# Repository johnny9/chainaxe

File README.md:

# ChainAxe — Rev A.1

Status: **engineering prototype; not a manufacturing release**  
Updated: 2026-08-16

ChainAxe is a clean-room ESP32-S3 controller for:

- one full S19- or S21-family Bitmain hashboard through the common data cable;
- four AntHat-style 12 V, four-wire Antminer fans with tach feedback and fail-safe full-speed startup;
- a 12–15 V low-current controller input; and
- native USB, Wi-Fi, and an ESP-Miner-derived mining application.

ChainAxe is an independent open-hardware project and is not affiliated with or endorsed by Bitmain. Antminer is a trademark of its respective owner.

The name refers to the complete ASIC hash chain controlled by the board. ChainAxe supersedes the earlier FT4232HQ-based **bitcrane** prototype with a clean ESP32-S3 architecture intended to run ESP-Miner directly.

There is **no PSU communication interface in Rev A.1**. Hashboard ASIC/core power remains on its normal external bus bars or bench supply. The ESP board communicates only through the hashboard data cable and drives the four fan connectors.

## Connector interpretation

The retained hashboard connector is physically **2×9 / 18 positions**. Pins 1–16 are used and positions 17–18 are NC, which explains the shorthand “16-pin header.” The user has confirmed this interface is compatible across the intended S19/S21 targets, so Rev A.1 standardizes the cable-side logic domain at 3.3 V and removes the previous target-voltage population matrix.

Compatibility here means the connector and electrical interface are shared. Firmware must still select the correct ASIC family, chip count, address stride, baud sequence, reset policy, and voltage/temperature-control path for the exact hashboard SKU.

## What is here

| Area | Deliverable |
|---|---|
| Architecture | Rail, signal, safety, and power-up decisions in `docs/architecture.md` |
| Target matrix | S19/S21 ASIC/profile scope in `docs/target-matrix.md` |
| Interfaces | Hashboard, fan, power, and USB pin tables in `docs/connector-pinout.md` |
| Schematic entry | Sheet plan and explicit net map in `schematic/` |
| BOM | JLC-oriented engineering BOM and upload template in `bom/` |
| PCB start | 100 × 70 mm floorplan, placement table, stack-up, and routing rules in `pcb/` and `docs/pcb-layout.md` |
| Firmware | ESP-Miner multi-profile porting plan in `firmware/esp-miner-porting-plan.md` |
| Release gates | Review and first-power checklist in `design-review-checklist.md` |
| Validation | Frozen hashes, automated results, and explicit open gates in `VALIDATION.md` |
| Provenance | Repository commits, licenses, and primary datasheets in `sources.md` |

## KiCad project

The editable KiCad 9 baseline is under `hardware/chainaxe/`:

- `chainaxe.kicad_pro` — project and net-class settings;
- `chainaxe.kicad_sch` — preliminary electrical schematic; and
- `chainaxe.kicad_pcb` — 100 × 70 mm unrouted placement baseline.

The KiCad files are intended for engineering review and iteration. They are not released Gerbers. Parts marked provisional or TBD in the engineering BOM must be resolved, the exact connector footprints must be fit-checked, and ERC/DRC must pass in KiCad before an order is placed. KiCad's CLI is not available in this workspace, so the included automated structural, pin-map, and placement-geometry checks are not ERC/DRC results.

The BOM distinguishes exact part candidates from provisional and TBD choices. There are no Gerbers, CPL, or fabrication ZIPs because the exact connector footprints, fan current path, and first supported hashboard profile still require engineering signoff.

## Rev A.1 block architecture

```mermaid
flowchart TD
    F12["12 V fan input"] --> FUSE["External fuse"]
    FUSE --> RPP["Reverse-polarity FETs"]
    RPP --> FANS["Four AntHat-style fan headers"]
    VIN["12–15 V logic input"] --> BUCK["3.3 V logic buck"]
    F12 -. "optional link at 12 V only" .-> BUCK
    USB["USB-C 5 V"] --> BUCK
    BUCK --> ESP["ESP32-S3"]
    ESP --> FANCTL["EMC2305 + fail-safe sinks"]
    ESP --> HBIO["3.3 V gated hashboard interface"]
    HBIO --> HB["18-position / 16-used cable"]
```

The hashboard's ASIC/core current does **not** pass through this controller. Controller ground, fan ground, and hashboard data-cable ground must be common.

## Power-input decision

- `J1 FAN_12V_IN`: high-current, regulated 12 V for the four fans.
- `J6 VIN_LOGIC_12_15`: low-current 12–15 V input for the AP64501 logic regulator.
- `JP1 FAN_TO_LOGIC`: optional fitted link/diode that powers logic from J1 when J1 is verified 12 V.
- USB-C can power logic for flashing with J1/J6 disconnected.

This split is intentional. A nominal 12 V fan must not receive 15 V unless its actual datasheet explicitly permits it. A single 12 V source can power both rails by fitting JP1; a 13–15 V hashboard system needs a separate regulated 12 V fan feed or a future high-current 12 V converter.

## Primary target profiles

- S19 XP / S19k-class BM1366 boards: ASIC driver exists in ESP-Miner; full-board chip counts and power control remain profile-specific.
- S21 BM1368 boards: ASIC driver exists; standard S21 evidence uses 108 chips and requires a NoPIC-aware startup path.
- S21 Pro / S21 XP / S21+ BM1370 boards: chip driver exists; each SKU has a different chip count.
- BM1398 and BM1362 S19-family boards require new ESP-Miner drivers before mining, even though the connector hardware is compatible. The family name alone is not sufficient to select the ASIC.

See `docs/target-matrix.md` for exact scope and evidence levels.

## Recommended first article

1. Review the KiCad schematic pin-by-pin, fit-check every connector and project-local footprint against current manufacturer drawings and real mating parts, and run ERC.
2. Assemble USB, ESP32-S3, AP64501, EMC2305, fan buffer/sinks, and the standardized 3.3 V hashboard interface.
3. Hand-install the 12 V fan, 12–15 V logic, fan, and hashboard connectors on five boards.
4. Validate USB-only and logic-only power first.
5. Validate four genuine Antminer fans from the dedicated 12 V input.
6. Bring up one named hashboard profile with core power current-limited and mining disabled until enumeration, temperatures, and fan interlocks pass.

## Key design choices

- ESP32-S3-WROOM-1-N16R8 retains ESP-Miner's UART pins 17/18.
- A SN74AXC4T774-class buffer operates at 3.3 V on both sides and provides explicit interface enable/disable.
- TPS22917 supplies connector pin 16 with controlled turn-on and reverse-current blocking.
- TMUX1511 is powered from switched `HB_3V3` and uses two of its powered-off-protected channels for the hashboard I²C pair. Local pull-ups stay on controller `3V3`; cable-side pull-ups stay on `HB_3V3`, so an unpowered cable domain cannot be phantom-powered through SDA/SCL.
- RESET has no universal hardware pulldown. Its bias and use are profile-dependent, and the series `RESET_ENABLE_LINK` is DNP/open in the default S21-safe assembly. It is populated with 33 Ω only for a specifically validated legacy-reset profile.
- EMC2305 outputs pass through a disabled-by-default SN74LVC126 and four 2N7002 sinks. With the ESP or buffer unpowered, fan PWM lines float and the fans run full speed.
- Fan motor power uses a calculated low-loss reverse-polarity FET stage, short wide top-and-bottom pours, and an upstream external fuse; it never flows through the AP64501.
- USB D+/− must be routed for 90 Ω differential, ±10%, over continuous ground; the ESP antenna sits at the board edge with a 15 mm keepout.

## Repository conclusions

- `bitaxeNaja` remains useful for ESP32-S3 pin conventions and translated ASIC I/O, but its dual-BM1340 chain is not a full-hashboard reference.
- `aditBoard` supplies the common 18-position/16-used connector map.
- `AntHat` supplies the EMC2305 fan-control pattern and the requested four 12 V fan connector arrangement. Its PSU section is not used.
- Current ESP-Miner supplies BM1366, BM1368, and BM1370 drivers but not BM1398 or BM1362.

## Licensing boundary

This is an original starter specification and does not redistribute the KiCad files or footprint artwork from `aditBoard` or `AntHat`, whose repositories do not state a hardware license. `bitaxeNaja` is CERN-OHL-S-2.0 and ESP-Miner is GPL-3.0; copying their covered hardware or software into a later release carries the corresponding obligations. See `sources.md`.

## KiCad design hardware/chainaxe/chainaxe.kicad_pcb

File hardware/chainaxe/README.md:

# ChainAxe KiCad project

This directory contains the editable Rev A.1 KiCad baseline.

## Files

- `chainaxe.kicad_pro` — KiCad project settings and provisional net classes.
- `chainaxe.kicad_sch` — annotated preliminary schematic.
- `chainaxe.kicad_pcb` — 100 × 70 mm unrouted placement baseline.
- `chainaxe.kicad_dru` — conservative prototype rules.
- `pin-net-audit.csv` — exhaustive expected/actual connection contract for every schematic pin.
- `symbols/ChainAxe.kicad_sym` and `sym-lib-table` — project-local custom symbols.
- `ChainAxe.pretty/` and `fp-lib-table` — nine pinned project-local manufacturer-derived/audited footprints.

Open `chainaxe.kicad_pro` in KiCad 9. KiCad may update generated metadata when the project is first saved; review that diff before committing it.

The source package is structurally checked by `scripts/validate_design.py`. The exhaustive `pin-net-audit.csv` contract is independently checked against physical symbol-pin endpoints by `scripts/validate_schematic_pinmap.py`; that validator explicitly converts KiCad library Y-up coordinates to schematic Y-down coordinates. `scripts/validate_pcb_geometry.py` checks different-net pad intersections, NPTH/copper conflicts, body/courtyard collisions, and undocumented edge overhangs. All three are dependency-free CI checks. This build environment does not include `kicad-cli`, so a local KiCad 9 ERC/DRC run remains mandatory before any fabrication export; none of the source validators replaces it.

Fan startup is hardware-defined: R105 holds `FAN_ARM` low, while R106–R109 hold the four EMC2305 PWM inputs to U8 low. This keeps the open-drain fan sinks released (the supported-fan full-speed-safe state) even if firmware asserts `FAN_ARM` before configuring the EMC2305. J30's audit enumerates every USB4105-GF-A signal/power contact; its A9/B9 VBUS and A12/B12 ground contacts are stacked on their shared logical nets. The official footprint numbers all four conductive shell stakes as `S1`, so one audited `S1` pin owns that common shell net.

C112 is the populated 100 nF USBLC6 VBUS bypass and must sit directly beside U9 pins 5/2. C3, the optional 220 µF 3V3 bulk footprint, is native DNP until AP64501 loop and load-transient validation proves an appropriate bulk value.

## Design status

This is an engineering-entry design, not an order-ready board. The schematic and PCB capture the intended architecture, safe startup states, connector map, and major candidate parts. The following remain release blockers:

- real-mating-part fit and keyed circuit-view checks for J1, J2–J6, J10, and USB-C; J6's exact connector/part remains a stop-order choice;
- fan current, inrush, reverse-polarity FET, connector, copper, and thermal calculations;
- AP64501 feedback, compensation, inductor, capacitance, and thermal verification;
- ESD/TVS clamping analysis and final ordering codes;
- exact first hashboard SKU/profile, including RESET policy and local voltage-off behavior;
- KiCad ERC, PCB synchronization, routing, stack-up impedance calculation, and DRC; and
- JLCPCB assembly preview, BOM/CPL reconciliation, and first-article review.

Do not generate production Gerbers from this baseline without closing the stop-order gates in `../../design-review-checklist.md`.

## PCB intent

The PCB is intentionally unrouted. The fan-current band stays at the top/right edge, the J10 interface lane stays at the left edge, and the ESP32-S3 antenna faces the bottom board edge with a 15 mm keepout. The `USB_90OHM_PLACEHOLDER` and `FAN_POWER_PROVISIONAL` net classes are reminders, not validated geometries.

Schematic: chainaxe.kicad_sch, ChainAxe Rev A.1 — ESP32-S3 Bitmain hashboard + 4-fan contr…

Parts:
C1, C2, C100, C102: 100n; C_0402_1005Metric
C3: 220uF LOW ESR — DNP POST-LOOP VALIDATION; CP_Elec_8x10.2; not fitted
C15: 100n 25V BOOTSTRAP; C_0402_1005Metric
C16: 10n SOFT START; C_0402_1005Metric
C17: 2.7n COMP — DS41980 TABLE 1; C_0402_1005Metric
C18: 56p COMP POLE DNP — DS41980 TABLE 1 C6; C_0402_1005Metric; not fitted
C20, C21: 470uF 25V LOW ESR; CP_Radial_D10.0mm_P5.00mm
C50: 1n CT TO VIN — PROVISIONAL; C_0402_1005Metric
C51: 1u U5 VIN BYPASS; C_0402_1005Metric
C52: 1u HB_3V3 LOCAL; C_0402_1005Metric
C70: 10n; C_0402_1005Metric
C80: 100n U6 VCCA; C_0402_1005Metric
C81: 100n U6 VCCB; C_0402_1005Metric
C101: 1u; C_0805_2012Metric
C103: 100n TMUX VDD; C_0402_1005Metric
C104: 100n U12 VCC; C_0402_1005Metric
C110: 1u EN delay; C_0402_1005Metric
C111: 1n 2kV SHIELD; C_0805_2012Metric
C112: 100nF 50V X7R — U9 VBUS BYPASS; C_0402_1005Metric; LCSC C307331
C200, C201, C202, C203: 100p TACH FILTER DNP; C_0402_1005Metric; not fitted
CIN1, CIN2, CIN3, CIN4: 10uF 50V X7R; C_1210_3225Metric
COUT1, COUT2, COUT3: 22uF 10V X7R; C_0805_2012Metric
D1: SS14 1A 40V; D_SMA; MPN SS14
D2, D3: SS14 1A 40V; D_SMA
D4: SMBJ13A PROVISIONAL; D_SMB; MPN SMBJ13A
D5: SMBJ18CA BIDIRECTIONAL PROVISIONAL; D_SMB; MPN SMBJ18CA
J1: FAN INPUT 12V ONLY — 0455580003; 0455580003_THT; MPN 0455580003; LCSC C492365
J2: FAN 1 — G 12 T P; 0353180420_THT; MPN 0353180420; LCSC C54909
J3: FAN 2 — G 12 T P; 0353180420_THT; MPN 0353180420; LCSC C54909
J4: FAN 3 — G 12 T P; 0353180420_THT; MPN 0353180420; LCSC C54909
J5: FAN 4 — G 12 T P; 0353180420_THT; MPN 0353180420; LCSC C54909
J6: LOGIC IN 12–15V — KEYED TBD; Molex_Micro-Fit_3.0_43650-0200_1x02_P3.00mm_Horizontal
J10: BITMAIN HASHBOARD DATA 2x9 / 18 POS; PM200-2-09-W-4.3_THT; MPN PM200-2-09-W-4.3; LCSC C3012192
J30: USB4105-GF-A — USB2 DEVICE; USB4105-GF-A; MPN USB4105-GF-A; LCSC C2988369
JP1: FAN_TO_LOGIC — DNP; SolderJumper-2_P1.3mm_Open_Pad1.0x1.5mm; not fitted
L1: 3.3uH SRP5030T-3R3M; L_Bourns-SRP5030TA_5.7x5.2mm; MPN SRP5030T-3R3M; LCSC C189931
Q1, Q2, Q3, Q4: 2N7002 OPEN-DRAIN PWM; SOT-23; MPN 2N7002; LCSC C8545
Q5, Q6: DMP3013SFV-7 PROVISIONAL; PowerDI3333-8_DMP3013SFV; MPN DMP3013SFV-7; LCSC C264098
R50: 100k; R_0402_1005Metric
R51: 100R QOD LINK — PROVISIONAL; R_0402_1005Metric
R60: 12k 1%; R_0402_1005Metric
R65: 10.5k COMP — DS41980 TABLE 1; R_0402_1005Metric
R70: 100k 1%; R_0402_1005Metric
R71: 27k 1%; R_0402_1005Metric
R80: 100k OE DISABLE; R_0402_1005Metric
R81: 33R TX; R_0402_1005Metric
R82: 33R RX PROVISIONAL; R_0402_1005Metric
R83: 100k ESP-SIDE PLUG PULLDOWN; R_0402_1005Metric
R84: 100k EN OFF; R_0402_1005Metric
R85, R86, R87, R88, R100, R101, R102: 4.7k; R_0402_1005Metric
R89: 10k RESET OE DISABLE; R_0402_1005Metric
R90: RESET_ENABLE_LINK — 33R DNP FOR S21; R_0402_1005Metric; not fitted
R91: 100k RESET BIAS-UP DNP; R_0402_1005Metric; not fitted
R92: 100k RESET BIAS-DN DNP; R_0402_1005Metric; not fitted
R93, R95, R97: 4.7k DEFAULT LOW; R_0402_1005Metric
R94, R96, R98: 0R HIGH OPTION DNP; R_0402_1005Metric; not fitted
R103: 22k CLK STRAP; R_0402_1005Metric
R104: 33k ADDR STRAP; R_0402_1005Metric
R105: 100k ARM OFF; R_0402_1005Metric
R106: 100k 1% PWM1 SAFE LOW; R_0402_1005Metric
R107: 100k 1% PWM2 SAFE LOW; R_0402_1005Metric
R108: 100k 1% PWM3 SAFE LOW; R_0402_1005Metric
R109: 100k 1% PWM4 SAFE LOW; R_0402_1005Metric
R110: 10k EN pull-up; R_0402_1005Metric
R111: 10k BOOT pull-up; R_0402_1005Metric
R112: 5.1k CC1; R_0402_1005Metric; LCSC C25905
R113: 5.1k CC2; R_0402_1005Metric; LCSC C25905
R114: 22R USB D+; R_0402_1005Metric; LCSC C25105
R115: 22R USB D-; R_0402_1005Metric; LCSC C25105
R116: 1M SHIELD; R_0402_1005Metric
R200, R203, R206, R209: 100k GATE OFF; R_0402_1005Metric
R201, R204, R207, R210: 36k TACH PULLUP; R_0402_1005Metric; LCSC C137999
RFB1: 69.8k 1% — DS41980 TABLE 1; R_0402_1005Metric
RFB2: 22.1k 1% — DS41980 TABLE 1; R_0402_1005Metric
SW1: BOOT; SW_SPST_CK_RS282G05A3; MPN CS1213AGF260; LCSC C5578986
SW2: RESET; SW_SPST_CK_RS282G05A3; MPN CS1213AGF260; LCSC C5578986
TP1: FAN_12V_RAW; TestPoint_Pad_D1.0mm
TP2: FAN_12V; TestPoint_Pad_D1.0mm
TP3: VIN_LOGIC_12_15; TestPoint_Pad_D1.0mm
TP4: LOGIC_IN; TestPoint_Pad_D1.0mm
TP5, TP13: 3V3; TestPoint_Pad_D1.0mm
TP6: HB_3V3; TestPoint_Pad_D1.0mm
TP7: RAIL_MON; TestPoint_Pad_D1.0mm
TP8: DBG_TX; TestPoint_Pad_D1.0mm
TP9: DBG_RX; TestPoint_Pad_D1.0mm
TP10: EXP_GPIO5; TestPoint_Pad_D1.0mm
TP11: EXP_GPIO6; TestPoint_Pad_D1.0mm
TP12: GND; TestPoint_Pad_D1.0mm
TP14: FAN_PWM1; TestPoint_Pad_D1.0mm
TP15: FAN_TACH1; TestPoint_Pad_D1.0mm
TP16: FAN_PWM2; TestPoint_Pad_D1.0mm
TP17: FAN_TACH2; TestPoint_Pad_D1.0mm
TP18: FAN_PWM3; TestPoint_Pad_D1.0mm
TP19: FAN_TACH3; TestPoint_Pad_D1.0mm
TP20: FAN_PWM4; TestPoint_Pad_D1.0mm
TP21: FAN_TACH4; TestPoint_Pad_D1.0mm
TP22: FAN_ARM; TestPoint_Pad_D1.0mm
TP23: FAN_ALERT_N; TestPoint_Pad_D1.0mm
TP24: FAN_SDA; TestPoint_Pad_D1.0mm
TP25: FAN_SCL; TestPoint_Pad_D1.0mm
TP26: USB_VBUS; TestPoint_Pad_D1.0mm
TP27: HB_RESET_CMD; TestPoint_Pad_D1.0mm
TP28: HB_IO_PWR_EN; TestPoint_Pad_D1.0mm
TP29: HB_TX; TestPoint_Pad_D1.0mm
TP30: HB_RX; TestPoint_Pad_D1.0mm
TP31: HB_PLUG; TestPoint_Pad_D1.0mm
TP32: HB_SDA; TestPoint_Pad_D1.0mm
TP33: HB_SCL; TestPoint_Pad_D1.0mm
TP34: HB_RESET; TestPoint_Pad_D1.0mm
TP35: HB_XLAT_OE_N; TestPoint_Pad_D1.0mm
TP36: HB_I2C_EN; TestPoint_Pad_D1.0mm
TP37: HB_RESET_OE_N; TestPoint_Pad_D1.0mm
U1: ESP32-S3-WROOM-1-N16R8; ESP32-S3-WROOM-1_v1.8; MPN ESP32-S3-WROOM-1-N16R8; LCSC C2913202
U2: EMC2305-1-AP-TR; EMC2305_QFN16_4x4_P0.65_EP2.2; MPN EMC2305-1-AP-TR; LCSC C621415
U3: AP64501SP-13 — 3V3 BUCK PROVISIONAL; AP64501_SO8EP; MPN AP64501SP-13; LCSC C2071517
U5: TPS22917DBVR — HB 3V3 SWITCH; SOT-23-6; MPN TPS22917DBVR; LCSC C2681320
U6: SN74AXC4T774PWR — UART/PLUG GATED; TSSOP-16_4.4x5mm_P0.65mm; MPN SN74AXC4T774PWR; LCSC C1849453
U7: TMUX1511PWR — GATED HB I2C; TSSOP-14_4.4x5mm_P0.65mm; MPN TMUX1511PWR; LCSC C2866750
U8: SN74LVC126APWR — FAN PWM ARM; TSSOP-14_4.4x5mm_P0.65mm; MPN SN74LVC126APWR
U9: USBLC6-2SC6; SOT-23-6; MPN USBLC6-2SC6; LCSC C7519
U10, U11, U13: TPD4E05U06DQAR; TI_DQA0010A_USON10_2.5x1.0_P0.5; MPN TPD4E05U06DQAR; LCSC C138714
U12: SN74LVC1G125DBVR — RESET GATE; SOT-23-5; MPN SN74LVC1G125DBVR
ZD1: BZX84C12LT1G 12V VGS clamp; SOT-23; MPN BZX84C12LT1G; LCSC C82475

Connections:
3V3: C1.1, C2.1, C3.1, C50.2, C51.1, C80.1, C100.1, C101.1, C102.1, COUT1.1, COUT2.1, COUT3.1, L1.2, R80.2, R85.2, R86.2, R89.2, R100.2, R101.2, R102.2, R103.2, R104.2, R110.1, R111.1, R201.2, R204.2, R207.2, R210.2, RFB1.1, TP5.1, TP13.1, U1.2 (3V3), U2.3 (VDD), U5.1 (VIN), U6.1 (DIR1), U6.8 (DIR4), U6.16 (VCCA), U8.14 (VCC)
BOOT_N: R111.2, SW1.1, U1.27 (GPIO0/BOOT*)
BUCK_BST: C15.1, U3.1 (BST)
BUCK_COMP: C18.1, R65.1, U3.6 (COMP)
BUCK_COMP_RC: C17.1, R65.2
BUCK_FB: RFB1.2, RFB2.1, U3.5 (FB)
BUCK_SS: C16.1, U3.4 (SS)
BUCK_SW: C15.2, L1.1, U3.8 (SW)
DBG_RX: TP9.1, U1.36 (U0RXD/GPIO44/CLK_OUT2)
DBG_TX: TP8.1, U1.37 (U0TXD/GPIO43/CLK_OUT1)
EMC_ADDR: R104.1, U2.4 (ADDR_SEL)
EMC_CLK: R103.1, U2.11 (CLK)
EMC_PWM1: R106.1, U2.5 (PWM1), U8.2 (1A)
EMC_PWM2: R107.1, U2.7 (PWM2), U8.5 (2A)
EMC_PWM3: R108.1, U2.9 (PWM3), U8.9 (3A)
EMC_PWM4: R109.1, U2.13 (PWM4), U8.12 (4A)
ESP_EN: C110.1, R110.2, SW2.1, U1.3 (EN)
EXP_GPIO5: TP10.1, U1.5 (GPIO5/TOUCH5/ADC1_CH4)
EXP_GPIO6: TP11.1, U1.6 (GPIO6/TOUCH6/ADC1_CH5)
FAN_12V: C20.1, C21.1, D4.1 (K), J2.2, J3.2, J4.2, J5.2, JP1.1 (A), Q5.1 (SOURCE), Q5.2 (SOURCE), Q5.3 (SOURCE), Q6.1 (SOURCE), Q6.2 (SOURCE), Q6.3 (SOURCE), R70.1, TP2.1, ZD1.3 (K)
FAN_12V_RAW: J1.4, J1.5, J1.6, Q5.5 (DRAIN), Q5.6 (DRAIN), Q5.7 (DRAIN), Q5.8 (DRAIN), Q6.5 (DRAIN), Q6.6 (DRAIN), Q6.7 (DRAIN), Q6.8 (DRAIN), TP1.1
FAN_ALERT_N: R102.1, TP23.1, U1.21 (GPIO13/TOUCH13/ADC2_CH2/FSPIQ/FSPIIO7/S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), U2.12 (~ALERT)
FAN_ARM: R105.1, TP22.1, U1.12 (GPIO8/TOUCH8/ADC1_CH7/SUBSPICS1), U8.1 (1OE), U8.4 (2OE), U8.10 (3OE), U8.13 (4OE)
FAN_GATE1: Q1.1 (G), R200.1, U8.3 (1Y)
FAN_GATE2: Q2.1 (G), R203.1, U8.6 (2Y)
FAN_GATE3: Q3.1 (G), R206.1, U8.8 (3Y)
FAN_GATE4: Q4.1 (G), R209.1, U8.11 (4Y)
FAN_PWM1: J2.4, Q1.3 (D), TP14.1
FAN_PWM2: J3.4, Q2.3 (D), TP16.1
FAN_PWM3: J4.4, Q3.3 (D), TP18.1
FAN_PWM4: J5.4, Q4.3 (D), TP20.1
FAN_RPP_GATE: Q5.4 (GATE), Q6.4 (GATE), R60.1, ZD1.1 (A)
FAN_SCL: R101.1, TP25.1, U1.25 (GPIO48/SPICLK_N/SUBSPICLK_N_DIFF), U2.2 (SMCLK)
FAN_SDA: R100.1, TP24.1, U1.24 (GPIO47/SPICLK_P/SUBSPICLK_P_DIFF), U2.1 (SMDATA)
FAN_TACH1: C200.1, J2.3, R201.1, TP15.1, U2.6 (TACH1)
FAN_TACH2: C201.1, J3.3, R204.1, TP17.1, U2.8 (TACH2)
FAN_TACH3: C202.1, J4.3, R207.1, TP19.1, U2.10 (TACH3)
FAN_TACH4: C203.1, J5.3, R210.1, TP21.1, U2.14 (TACH4)
FAN_TO_LOGIC_FEED: D2.2 (A), JP1.2 (B)
GND: C1.2, C2.2, C3.2, C16.2, C17.2, C18.2, C20.2, C21.2, C51.2, C52.2, C70.2, C80.2, C81.2, C100.2, C101.2, C102.2, C103.2, C104.2, C110.2, C111.2, C112.2, C200.2, C201.2, C202.2, C203.2, CIN1.2, CIN2.2, CIN3.2, CIN4.2, COUT1.2, COUT2.2, COUT3.2, D4.2 (A), D5.2 (A2), J1.1, J1.2, J1.3, J2.1, J3.1, J4.1, J5.1, J6.2, J10.1, J10.2, J10.9, J10.10, J10.13, J10.14, J30.A1 (GND), J30.A12 (GND), J30.B1 (GND), J30.B12 (GND), Q1.2 (S), Q2.2 (S), Q3.2 (S), Q4.2 (S), R50.2, R60.2, R71.2, R83.2, R84.2, R92.2, R93.2, R95.2, R97.2, R105.2, R106.2, R107.2, R108.2, R109.2, R112.2, R113.2, R116.2, R200.2, R203.2, R206.2, R209.2, RFB2.2, SW1.2, SW2.2, TP12.1, U1.1 (GND), U1.40 (GND), U1.41 (GND), U2.17 (GND), U3.7 (GND), U3.9 (EP), U5.2 (GND), U6.2 (DIR2), U6.6 (A4), U6.7 (DIR3), U6.10 (GND), U7.7 (GND), U7.10 (SEL3), U7.13 (SEL4), U8.7 (GND), U9.2 (GND), U10.3 (GND), U10.8 (GND), U11.3 (GND), U11.8 (GND), U12.3 (GND), U13.3 (GND), U13.8 (GND)
HB_3V3: C52.1, C81.1, C103.1, C104.1, J10.16, R51.1, R87.2, R88.2, R91.2, R94.2, R96.2, R98.2, TP6.1, U5.6 (VOUT), U6.15 (VCCB), U7.14 (VDD), U12.5 (VCC)
HB_3V3_CT: C50.1, U5.4 (CT)
HB_A0: J10.8, R93.1, R94.1, U11.2 (D1-)
HB_A1: J10.7, R95.1, R96.1, U11.1 (D1+)
HB_A2: J10.6, R97.1, R98.1, U10.5 (D2-)
HB_I2C_EN: R84.1, TP36.1, U1.17 (GPIO9/TOUCH9/ADC1_CH8/FSPIHD/SUBSPIHD), U7.1 (SEL1), U7.4 (SEL2)
HB_IO_PWR_EN: R50.1, TP28.1, U1.18 (GPIO10/TOUCH10/ADC1_CH9/FSPICS0/FSPIIO4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), U5.3 (ON)
HB_PLUG: J10.5, TP31.1, U6.12 (B3), U10.4 (D2+)
HB_PLUG_3V3: R83.1, U1.20 (GPIO12/TOUCH12/ADC2_CH1/FSPICLK/FSPIIO6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), U6.5 (A3)
HB_QOD: R51.2, U5.5 (QOD)
HB_RESET: J10.15, R90.2, R91.1, R92.1, TP34.1, U13.1 (D1+)
HB_RESET_CMD: TP27.1, U1.39 (GPIO1/TOUCH1/ADC1_CH0), U12.2 (A)
HB_RESET_DRV: R90.1, U12.4 (Y)
HB_RESET_OE_N: R89.1, TP37.1, U1.4 (GPIO4/TOUCH4/ADC1_CH3), U12.1 (OE_N)
HB_RX: J10.12, R82.1, TP30.1, U11.5 (D2-)
HB_RX_3V3: U1.11 (GPIO18/U1RXD/ADC2_CH7/CLK_OUT3), U6.4 (A2)
HB_RX_BUF: R82.2, U6.13 (B2)
HB_SCL: J10.4, R87.1, TP33.1, U7.3 (D1), U10.2 (D1-)
HB_SCL_3V3: R85.1, U1.23 (GPIO21), U7.2 (S1)
HB_SDA: J10.3, R88.1, TP32.1, U7.6 (D2), U10.1 (D1+)
HB_SDA_3V3: R86.1, U1.22 (GPIO14/TOUCH14/ADC2_CH3/FSPIWP/FSPIDQS/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), U7.5 (S2)
HB_TX: J10.11, R81.2, TP29.1, U11.4 (D2+)
HB_TX_3V3: U1.10 (GPIO17/U1TXD/ADC2_CH6), U6.3 (A1)
HB_TX_BUF: R81.1, U6.14 (B1)
HB_XLAT_OE_N: R80.1, TP35.1, U1.7 (GPIO7/TOUCH7/ADC1_CH6), U6.9 (OE)
LOGIC_IN: CIN1.1, CIN2.1, CIN3.1, CIN4.1, D1.1 (K), D2.1 (K), D3.1 (K), TP4.1, U3.2 (VIN), U3.3 (EN)
RAIL_MON: C70.1, R70.2, R71.1, TP7.1, U1.19 (GPIO11/TOUCH11/ADC2_CH0/FSPID/FSPIIO5/S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)
USB_CC1: J30.A5 (CC1), R112.1
USB_CC2: J30.B5 (CC2), R113.1
USB_DN: R115.2, U1.13 (GPIO19/U1RTS/ADC2_CH8/CLK_OUT2/USB_D-)
USB_DN_CONN: J30.A7 (D-), J30.B7 (D-), U9.3 (I/O2)
USB_DN_PROT: R115.1, U9.4 (I/O2)
USB_DP: R114.2, U1.14 (GPIO20/U1CTS/ADC2_CH9/CLK_OUT1/USB_D+)
USB_DP_CONN: J30.A6 (D+), J30.B6 (D+), U9.1 (I/O1)
USB_DP_PROT: R114.1, U9.6 (I/O1)
USB_SHIELD: C111.1, J30.S1 (SHIELD), R116.1
USB_VBUS: C112.1, D3.2 (A), J30.A4 (VBUS), J30.A9 (VBUS), J30.B4 (VBUS), J30.B9 (VBUS), TP26.1, U9.5 (VBUS)
VIN_LOGIC_12_15: D1.2 (A), D5.1 (A1), J6.1, TP3.1

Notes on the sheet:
CHAINAXE REV A.1 — PRELIMINARY / NOT FOR FABRICATION
POWER + PROTECTION (J1 regulated 12V fan power; J6 controller-only 12–15V)
ESP32-S3 + USB / DEBUG
HASHBOARD CABLE INTERFACE — COMMON 2x9 / 18-POSITION FORM
FAN CONTROL — 4x ANTHAT-STYLE 12V 4-WIRE
DANGER / S21 ASSEMBLY RULE: leave R90 RESET_ENABLE_LINK OPEN/DNP. Firmware must also never enable U12. Hardware safety is not firmware-only.
SAFE STARTUP: R105 keeps FAN_ARM=0 and R106-R109 hold U8 PWM inputs low; sinks stay released/full-speed-safe. HB_3V3=OFF; U6/U7/U12 disabled or high-Z. Prove every state on hardware.
NO PSU CONTROL ON REV A.1. Hashboard core power remains external; an interface fault cannot guarantee removal of ASIC core power.
J1/fan copper is high current. External fuse required near source. Select FET count, connector, copper, and thermals from measured simultaneous startup/stall current.
FAN PROFILE RULE: supported 4-wire fans must include their own PWM pull-up. ChainAxe provides open-drain sinks only; fans needing an external pull-up are unsupported.
HASHBOARD POWER RULE: J10 pin16 HB_3V3 is controller-sourced only through U5. Never externally drive or backfeed this rail while R51 QOD is populated.
All connector drawings are mating-face views. Continuity-check pin 1, keying, fan G/12/T/P, J10 positions 17/18 NC, and shared ground before power.
PROVISIONAL/TBD: J6 selection and all connector fit checks; AP64501 compensation/magnetics; TVS ratings; FET thermals; EMC2305 straps; exact S19/S21 profile.
JLCPCB intent: 4-layer, mostly 0402/0805; extended parts accepted; J1/J2-J5/J10 hand-install. Verify fresh manufacturer-drawing footprints with 1:1 prints.
Source basis: bitaxeorg/bitaxeNaja, skot/aditBoard, skot/AntHat, and manufacturer datasheets. Independently audit every critical symbol and footprint before fabrication.

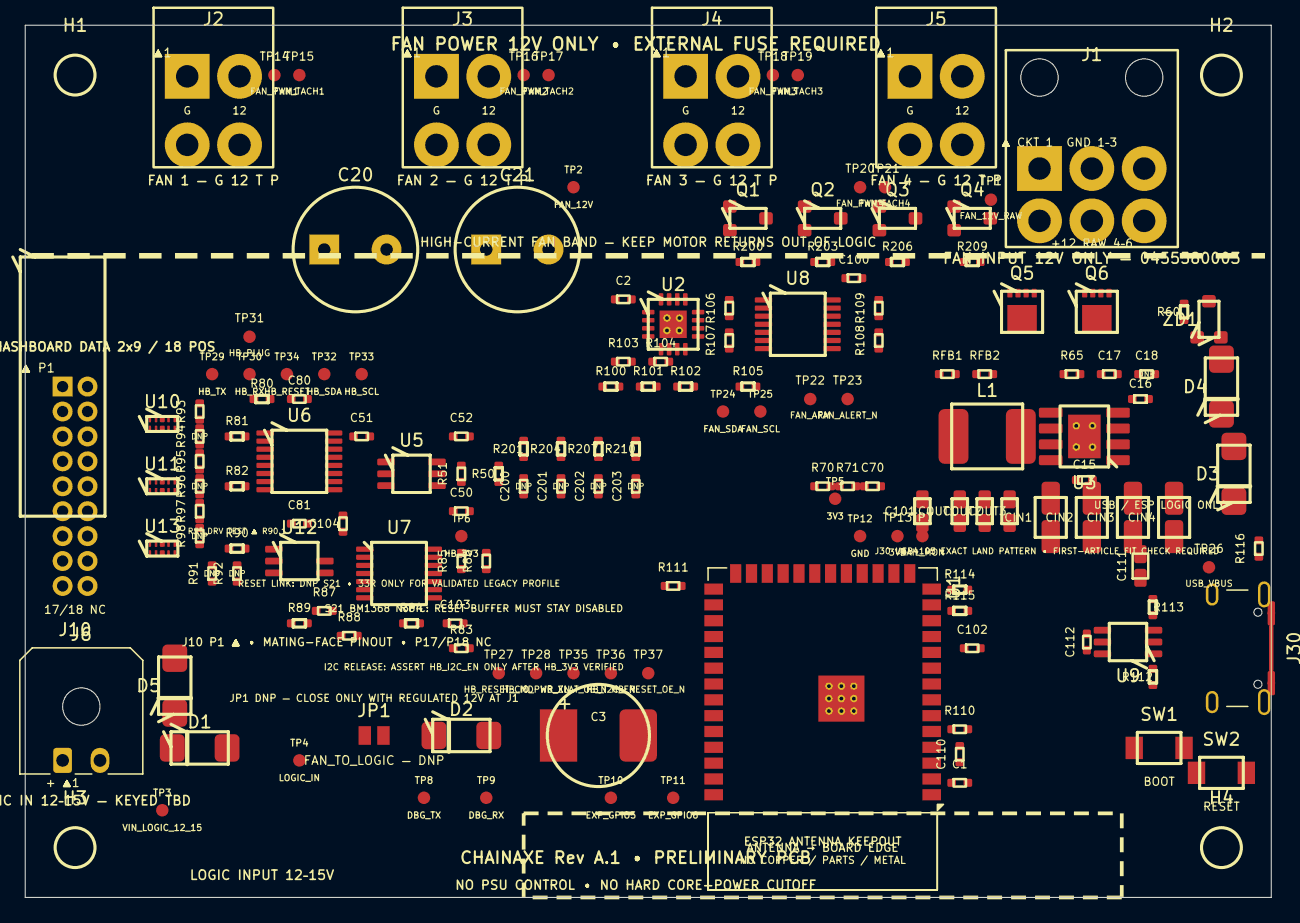
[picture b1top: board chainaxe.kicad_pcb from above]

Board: 4 copper layers, 100.0 x 70.0 mm, 163 parts (0 on the bottom side), 78 nets, no tracks yet.

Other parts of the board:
H1, H2, H3, H4: M3; MountingHole_3.2mm_M3

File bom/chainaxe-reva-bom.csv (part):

Status,Designator,Qty,Function,Value,Manufacturer,MPN,Footprint,LCSC Part #,Assembly,Population,Notes
EXACT_CANDIDATE,U1,1,MCU module,ESP32-S3-WROOM-1-N16R8,Espressif,ESP32-S3-WROOM-1-N16R8,ChainAxe:ESP32-S3-WROOM-1_v1.8,C2913202,SMT extended,POPULATE,"Project-local footprint follows Espressif v1.8 land pattern with 3.7 mm center pad/vias and antenna keepout; verify metal-chassis strategy"
PROVISIONAL,U2,1,Four-channel fan controller,EMC2305,Microchip,EMC2305-1-AP-TR,ChainAxe:EMC2305_QFN16_4x4_P0.65_EP2.2,C621415,SMT extended,POPULATE,"AP-specific 2.2 mm exposed land with paste windowing and thermal vias; use channels 1-4; fifth channel NC"
PROVISIONAL,U3,1,3.3 V synchronous buck,AP64501,Diodes Incorporated,AP64501SP-13,ChainAxe:AP64501_SO8EP,C2071517,SMT extended,POPULATE,"Project-local Diodes land/paste/thermal-via pattern; DS41980 Table 1 starting cell is implemented; validate loop stability, transients, and thermal margin"
PROVISIONAL,L1,1,Buck inductor,3.3 uH,Bourns,SRP5030T-3R3M,Inductor_SMD:L_Bourns-SRP5030TA_5.7x5.2mm,C189931,SMT extended,POPULATE,"Recalculate saturation and RMS current for the final 3.3 V design"
PROVISIONAL,U5,1,Switched hashboard logic supply,3.3 V 2 A load switch,Texas Instruments,TPS22917DBVR,Package_TO_SOT_SMD:SOT-23-6,C2681320,SMT extended,POPULATE,"Controller sources J10 pin 16; R50 holds the switch off at reset"
PROVISIONAL,U6,1,Gated hashboard UART/PLUG interface,SN74AXC4T774,Texas Instruments,SN74AXC4T774PWR,Package_SO:TSSOP-16_4.4x5mm_P0.65mm,C1849453,SMT extended,POPULATE,"Both domains are 3.3 V; directions and OE mapping are frozen in the schematic"
EXACT_CANDIDATE,U7,1,Powered-off-protected hashboard I2C switch,TMUX1511,Texas Instruments,TMUX1511PWR,Package_SO:TSSOP-14_4.4x5mm_P0.65mm,C2866750,SMT extended,POPULATE,"VDD from switched HB_3V3; channels 1/2 carry SCL/SDA; R84 disables both used channels by default"
EXACT_CANDIDATE,U8,1,Four-channel active-high tri-state fan buffer,SN74LVC126A,Texas Instruments,SN74LVC126APWR,Package_SO:TSSOP-14_4.4x5mm_P0.65mm,C7815,SMT extended,POPULATE,"R105 leaves all 2N7002 sinks off; verify float-PWM full-speed behavior with the exact fan"
EXACT_CANDIDATE,U12,1,Independent gated hashboard reset buffer,SN74LVC1G125,Texas Instruments,SN74LVC1G125DBVR,Package_TO_SOT_SMD:SOT-23-5,C23654,SMT extended,POPULATE,"R89 is the mandatory 10k active-low OE pullup; default S21 assembly leaves R90 open/DNP"
EXACT_CANDIDATE,"Q1,Q2,Q3,Q4",4,Fan open-drain PWM sinks,2N7002,Nexperia or approved,2N7002,Package_TO_SOT_SMD:SOT-23,C8545,SMT basic,POPULATE,"R200/R203/R206/R209 are gate pulldowns; drain connects to each fan PWM line"
PROVISIONAL,"Q5,Q6",2,Parallel high-side fan-input reverse-polarity FETs,-30 V P-channel,Diodes Incorporated,DMP3013SFV-7,ChainAxe:PowerDI3333-8_DMP3013SFV,C264098,SMT extended,SELECT_BEFORE_RELEASE,"Use exact Diodes Type-UX mapping; validate paste, SOA, current sharing, Rds(on), copper, and simultaneous fan startup/stall thermals"
EXACT_CANDIDATE,ZD1,1,Fan-input MOSFET gate clamp,12 V Zener,onsemi,BZX84C12LT1G,Package_TO_SOT_SMD:SOT-23,C82475,SMT extended,SELECT_BEFORE_RELEASE,"Pin 1 anode to gate; pin 2 NC; pin 3 cathode to protected FAN_12V; validate dissipation and transients"
EXACT_CANDIDATE,U9,1,USB low-capacitance ESD,USBLC6-2SC6,STMicroelectronics,USBLC6-2SC6,Package_TO_SOT_SMD:SOT-23-6,C7519,SMT extended,POPULATE,"Place immediately behind the USB receptacle"
EXACT_CANDIDATE,"U10,U11,U13",3,Cable-side 3.3 V ESD array,TPD4E05U06,Texas Instruments,TPD4E05U06DQAR,ChainAxe:TI_DQA0010A_USON10_2.5x1.0_P0.5,C138714,SMT extended,POPULATE,"TI DQA0010A map and land: shunts 1/2/4/5; enlarged GND 3/8; NC 6/7/9/10; verify pin 1 at J10"
PROVISIONAL,"D1,D2,D3",3,Logic-source OR Schottky,1 A 40 V,Multiple,SS14,Diode_SMD:D_SMA,TBD,SMT,POPULATE,"D1 gives J6 reverse blocking; D2 is JP1-qualified FAN_12V; D3 is USB_VBUS; select exact MPN/LCSC and verify AP64501 headroom"
PROVISIONAL,D4,1,Protected fan-bus TVS,13 V standoff starting point,Multiple,SMBJ13A,Diode_SMD:D_SMB,TBD,SMT,SELECT_BEFORE_RELEASE,"Coordinate standoff and clamp energy with the exact 12 V fans and upstream fuse; J1 is not a 15 V fan input"
PROVISIONAL,D5,1,Logic-input bidirectional TVS,18 V standoff starting point,Multiple,SMBJ18CA,Diode_SMD:D_SMB,TBD,SMT,SELECT_BEFORE_RELEASE,"Bidirectional part at J6; verify pulse energy and clamping before release"
PROVISIONAL,J30,1,USB-C USB2 receptacle,USB4105-GF-A,Global Connector Technology,USB4105-GF-A,ChainAxe:USB4105-GF-A,C2988369,SMT extended,STOP_ORDER,"STOP-ORDER until first-article fit check: project-local footprint vendors the official KiCad 8.0.9/GCT geometry with all contacts, THT shell stakes, and NPTH locating pegs"
PROVISIONAL,J10,1,Bitmain hashboard data connector,2x9 2.00 mm right-angle,HCTL,PM200-2-09-W-4.3,ChainAxe:PM200-2-09-W-4.3_THT,C3012192,THT/manual,HAND_INSTALL,"18 physical positions; pins 1-16 used and 17-18 NC; project-local drawing-derived footprint still needs mating-face orientation and real-cable fit checks"
EXACT_CANDIDATE,J1,1,High-current fan supply input,2x3 keyed THT,Molex,0455580003,ChainAxe:0455580003_THT,C492365,THT/manual,HAND_INSTALL,"Regulated 12 V only; project-local footprint follows Molex SD-45558-001 contact and peg geometry; verify circuit-1 orientation and fit a real connector"
TBD,J6,1,Low-current controller supply input,2-pin keyed 18-24 AWG,TBD,TBD,Connector_Molex:Molex_Micro-Fit_3.0_43650-0200_1x02_P3.00mm_Horizontal,TBD,THT/manual,STOP_ORDER,"STOP-ORDER: accepts 12-15 V for logic only; current Micro-Fit footprint is a placeholder until an exact keyed connector and mate are selected"
EXACT_CANDIDATE,"J2,J3,J4,J5",4,AntHat-style four-wire fan connectors,Keyed 2x2 nominal 4.2 mm pitch,Molex,0353180420,ChainAxe:0353180420_THT,C54909,THT/manual,HAND_INSTALL,"Silk G/12/T/P; project-local footprint follows Molex SD-35318 4.2 x 5.5 mm pattern; verify key, circuit view, and real fan harness"
TBD,JP1,1,Optional fan-to-logic feed,Open solder jumper,N/A,N/A,Jumper:SolderJumper-2_P1.3mm_Open_Pad1.0x1.5mm,N/A,Manual,DNP,"Fit only when J1 is verified regulated 12 V; feeds FAN_12V through D2 and never bypasses the diode"
TBD,"SW1,SW2",2,BOOT and RESET buttons,Momentary NO,TBD,TBD,Button_Switch_SMD:SW_SPST_CK_RS282G05A3,TBD,SMT,STOP_ORDER,"STOP-ORDER: schematic uses the CK RS282G05A3 footprint; prior CS1213AGF260/C5578986 pairing is not footprint-verified and is removed from the JLC template"
EXACT_CANDIDATE,R60,1,Fan-input reverse-protection gate resistor,12k 1%,UNI-ROYAL,0402WGF1202TCE,Resistor_SMD:R_0402_1005Metric,C25752,SMT basic,SELECT_BEFORE_RELEASE,"Q5/Q6 gate pull; validate with ZD1 and final FET topology"
EXACT_CANDIDATE,"R50,R80,R83,R84,R105,R106,R107,R108,R109,R200,R203,R206,R209",13,Hardware safe-state pulls,100k 1%,UNI-ROYAL,0402WGF1003TCE,Resistor_SMD:R_0402_1005Metric,C25741,SMT basic,POPULATE,"U5 off; U6 off; PLUG defined; U7 off; fan arm off; R106-R109 define U8 inputs low until EMC2305 push-pull configuration; four fan gates off"
PROVISIONAL,R70,1,Rail-monitor divider top,100k 1%,UNI-ROYAL,0402WGF1003TCE,Resistor_SMD:R_0402_1005Metric,C25741,SMT basic,POPULATE,"With R71 and C70; validate ADC full-scale against the selected monitored rail"
PROVISIONAL,"R91,R92",2,Optional hashboard reset bias pads,100k starting value,UNI-ROYAL,0402WGF1003TCE,Resistor_SMD:R_0402_1005Metric,C25741,SMT basic,DNP,"Mutually exclusive reset bias-up/down options; default S21-safe assembly leaves both open"
EXACT_CANDIDATE,"R89,R110,R111",3,Reset-OE and MCU EN/BOOT pullups,10k 1%,UNI-ROYAL,0402WGF1002TCE,Resistor_SMD:R_0402_1005Metric,C25744,SMT basic,POPULATE,"R89 disables U12; R110 is ESP EN pullup; R111 is BOOT pullup"
PROVISIONAL,R51,1,Hashboard 3.3 V quick-output-discharge link,100 ohm 1%,Multiple,TBD,Resistor_SMD:R_0402_1005Metric,TBD,SMT,POPULATE,"VOUT to TPS22917 QOD; J10 pin 16 must never be externally driven"
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

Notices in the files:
parts and their libraries:
GCT USB4105-GF-A exact official KiCad 8.0.9 manufacturer-drawing-derived geometry; four conductive shell stakes share S1; includes two 0.65 mm NPTH locating pegs. Vendored from KiCad Connector_USB under CC-BY-SA 4.0; first-article fit check required.
